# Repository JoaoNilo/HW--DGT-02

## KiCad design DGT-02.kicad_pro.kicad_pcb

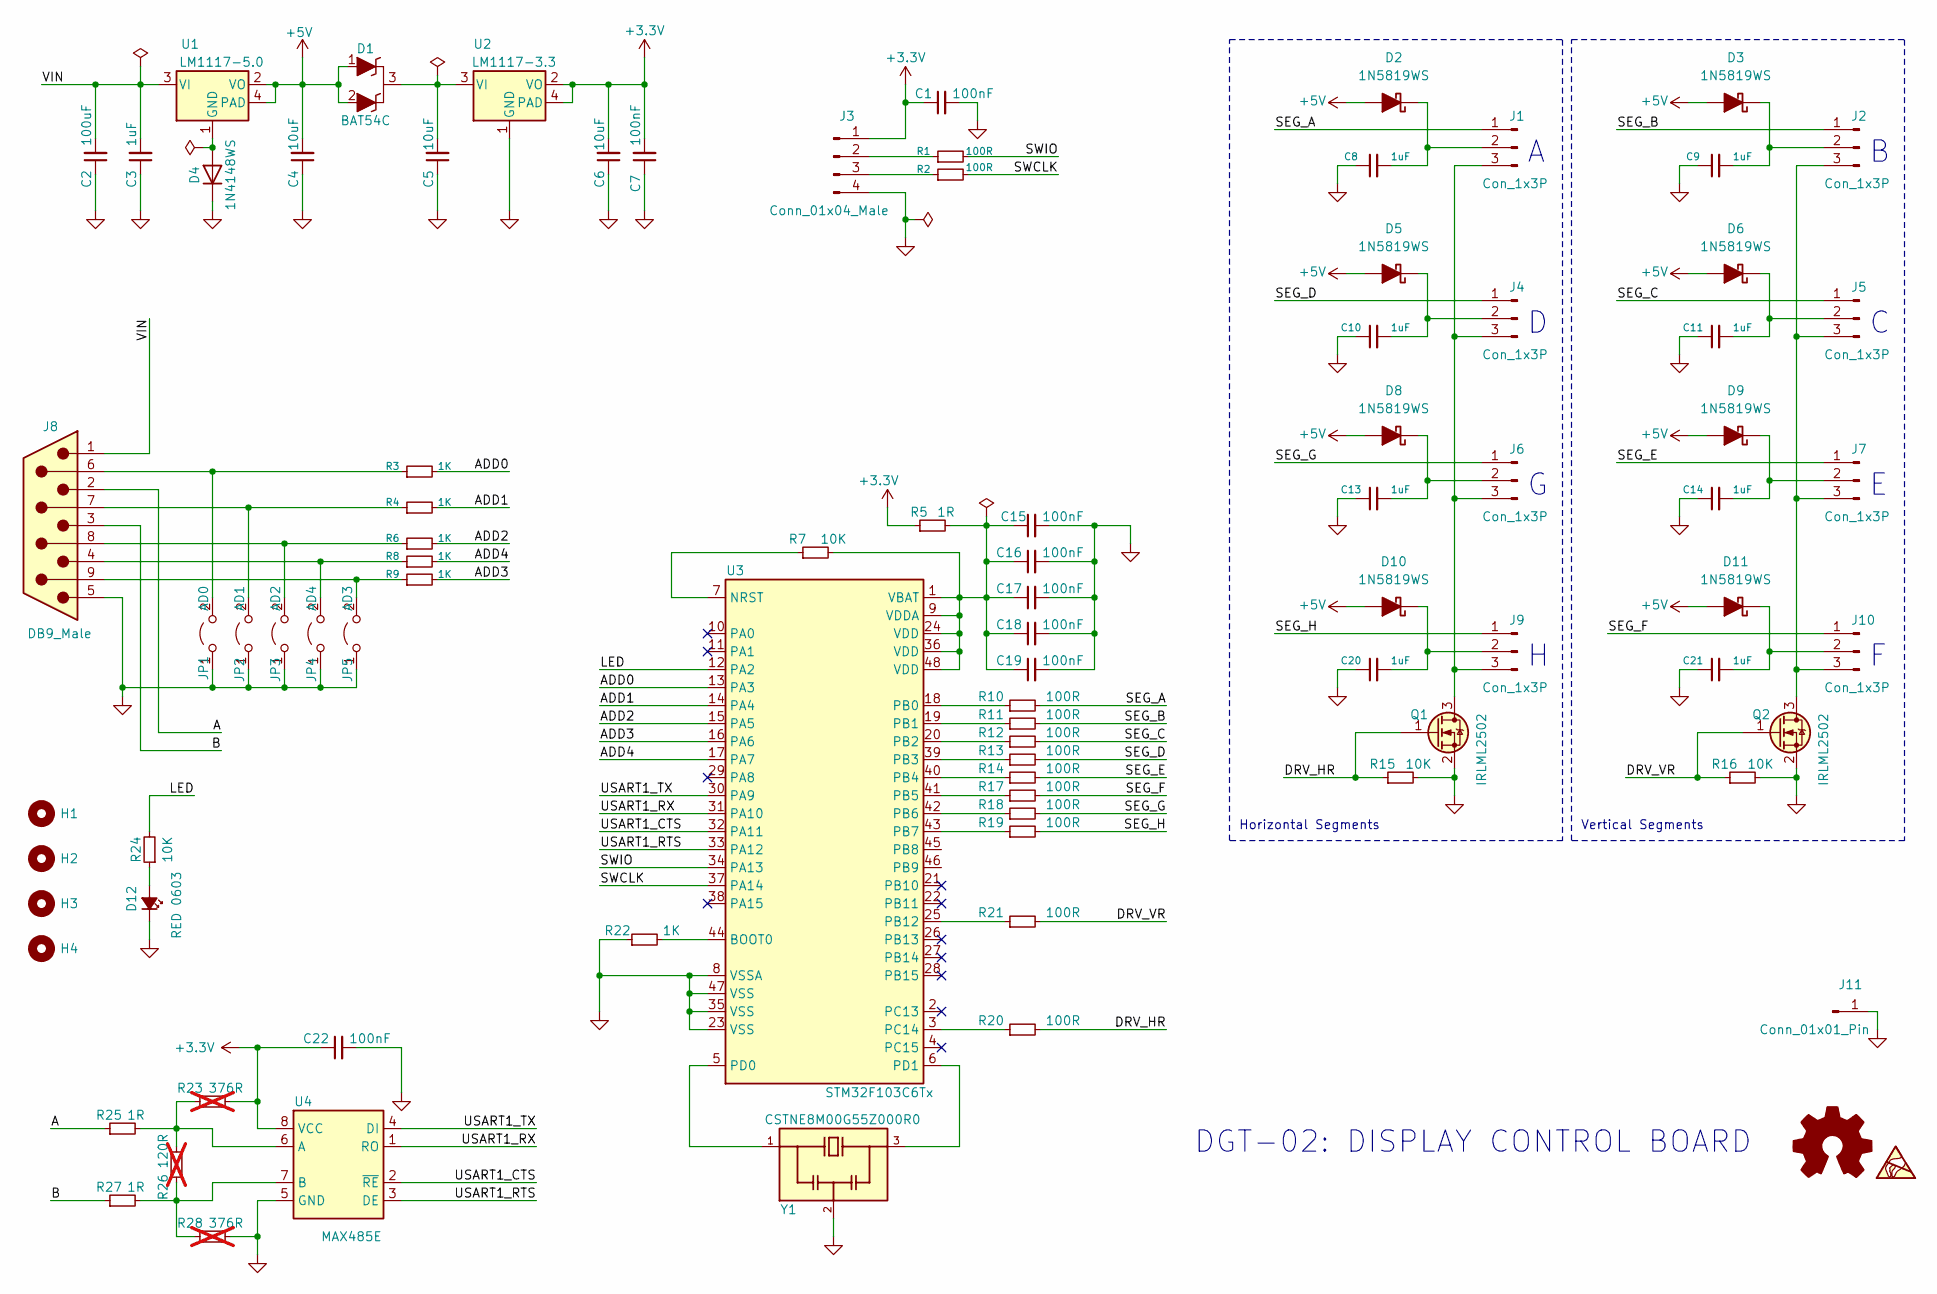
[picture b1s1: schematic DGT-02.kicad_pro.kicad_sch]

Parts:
C1, C7, C15, C16, C17, C18, C19, C22: 100nF; C_0603_1608Metric
C2: 100uF; C_1210_3225Metric
C3: 1uF; C_0805_2012Metric
C4, C5, C6: 10uF; C_1206_3216Metric
C8, C9, C10, C11, C13, C14, C20, C21: 1uF; C_0603_1608Metric
D1: BAT54C; SOT-23
D2, D3, D5, D6, D8, D9, D10, D11: 1N5819WS; D_SOD-323
D4: 1N4148WS; D_SOD-323
D12: RED 0603; LED_0603_1608Metric
H1, H2, H3, H4: MountingHole; MountingHole_2.2mm_M2
J1, J2, J4, J5, J6, J7, J9, J10: Con_1x3P; PinHeader_1x03_P2.54mm_Horizontal_Nilo
J3: Conn_01x04_Male; PinHeader_1x04_P2.54mm_Vertical
J8: DB9_Male; DSUB-9_Male_Horizontal_P2.77x2.84mm_EdgePinOffset7.70mm_Hou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
J11: Conn_01x01_Pin; PinHeader_1x01_P2.54mm_Vertical
JP1: AD0; SolderJumper-2_P1.3mm_Open_TrianglePad1.0x1.5mm
JP2: AD1; SolderJumper-2_P1.3mm_Open_TrianglePad1.0x1.5mm
JP3: AD2; SolderJumper-2_P1.3mm_Open_TrianglePad1.0x1.5mm
JP4: AD4; SolderJumper-2_P1.3mm_Open_TrianglePad1.0x1.5mm
JP5: AD3; SolderJumper-2_P1.3mm_Open_TrianglePad1.0x1.5mm
LOGO1: Logo_Open_Hardware_Small; KiCad-Logo2_5mm_SilkScreen
Q1, Q2: IRLML2502; SOT-23
R1, R2, R10, R11, R12, R13, R14, R17, R18, R19, R20, R21: 100R; R_0603_1608Metric
R3, R4, R6, R8, R9, R22: 1K; R_0603_1608Metric
R5, R25, R27: 1R; R_0603_1608Metric
R7, R15, R16, R24: 10K; R_0603_1608Metric
R23, R28: 376R; R_0603_1608Metric; not fitted
R26: 120R; R_0603_1608Metric; not fitted
SYM1: SYM_ESD_Small; ESD-Logo_6.6x6mm_SilkScreen
U1: LM1117-5.0; SOT-223
U2: LM1117-3.3; SOT-223
U3: STM32F103C6Tx; LQFP-48_7x7mm_P0.5mm
U4: MAX485E; SOIC-8_3.9x4.9mm_P1.27mm
Y1: CSTNE8M00G55Z000R0; OSC_CSTNE8M00G55Z000R0; PARTREV JGC42-8858A

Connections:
+3V3: C1.1, C6.2, C7.2, C22.1, J3.1, R5.1, R23.2, U2.2 (VO), U2.4 (PAD), U4.8 (VCC)
+5V: C4.2, D1.1 (A), D1.2 (A), D2.2 (A), D3.2 (A), D5.2 (A), D6.2 (A), D8.2 (A), D9.2 (A), D10.2 (A), D11.2 (A), U1.2 (VO), U1.4 (PAD)
/A: J8.2, R25.1
/ADD0: R3.2, U3.13 (PA3)
/ADD1: R4.2, U3.14 (PA4)
/ADD2: R6.2, U3.15 (PA5)
/ADD3: R9.2, U3.16 (PA6)
/ADD4: R8.2, U3.17 (PA7)
/B: J8.3, R27.1
/DRV_HR: Q1.1 (G), R15.1, R20.2
/DRV_VR: Q2.1 (G), R16.1, R21.2
/LED: R24.2, U3.12 (PA2)
/SEG_A: J1.1, R10.2
/SEG_B: J2.1, R11.2
/SEG_C: J5.1, R12.2
/SEG_D: J4.1, R13.2
/SEG_E: J7.1, R14.2
/SEG_F: J10.1, R17.2
/SEG_G: J6.1, R18.2
/SEG_H: J9.1, R19.2
/SWCLK: R2.2, U3.37 (PA14)
/SWIO: R1.2, U3.34 (PA13)
/USART1_CTS: U3.32 (PA11), U4.2 (~RE)
/USART1_RTS: U3.33 (PA12), U4.3 (DE)
/USART1_RX: U3.31 (PA10), U4.1 (RO)
/USART1_TX: U3.30 (PA9), U4.4 (DI)
/VIN: C2.2, C3.2, J8.1, U1.3 (VI)
unnamed: C5.2, D1.3 (K), U2.3 (VI)
unnamed: C8.2, D2.1 (K), J1.2
unnamed: C9.2, D3.1 (K), J2.2
unnamed: D4.2 (A), U1.1 (GND)
unnamed: C10.2, D5.1 (K), J4.2
unnamed: C11.2, D6.1 (K), J5.2
unnamed: C13.2, D8.1 (K), J6.2
unnamed: C14.2, D9.1 (K), J7.2
unnamed: C20.2, D10.1 (K), J9.2
unnamed: C21.2, D11.1 (K), J10.2
unnamed: D12.2 (A), R24.1
unnamed: J3.2, R1.1
unnamed: J3.3, R2.1
unnamed: J8.6, JP1.2 (B), R3.1
unnamed: J8.7, JP2.2 (B), R4.1
unnamed: J8.8, JP3.2 (B), R6.1
unnamed: J8.4, JP4.2 (B), R8.1
unnamed: J8.9, JP5.2 (B), R9.1
unnamed: R22.2, U3.44 (BOOT0)
unnamed: R7.1, U3.7 (NRST)
unnamed: R10.1, U3.18 (PB0)
unnamed: R11.1, U3.19 (PB1)
unnamed: R12.1, U3.20 (PB2)
unnamed: R13.1, U3.39 (PB3)
unnamed: R14.1, U3.40 (PB4)
unnamed: R17.1, U3.41 (PB5)
unnamed: R18.1, U3.42 (PB6)
unnamed: R19.1, U3.43 (PB7)
unnamed: R21.1, U3.25 (PB12)
unnamed: R20.1, U3.3 (PC14)
unnamed: U3.5 (PD0), Y1.1
unnamed: U3.6 (PD1), Y1.3
unnamed: C15.1, C16.1, C17.1, C18.1, C19.1, R5.2, R7.2, U3.1 (VBAT), U3.9 (VDDA), U3.24 (VDD), U3.36 (VDD), U3.48 (VDD)
unnamed: R23.1, R25.2, R26.2, U4.6 (A)
unnamed: R26.1, R27.2, R28.1, U4.7 (B)

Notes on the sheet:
Vertical Segments
Horizontal Segments
DGT-02: DISPLAY CONTROL BOARD

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
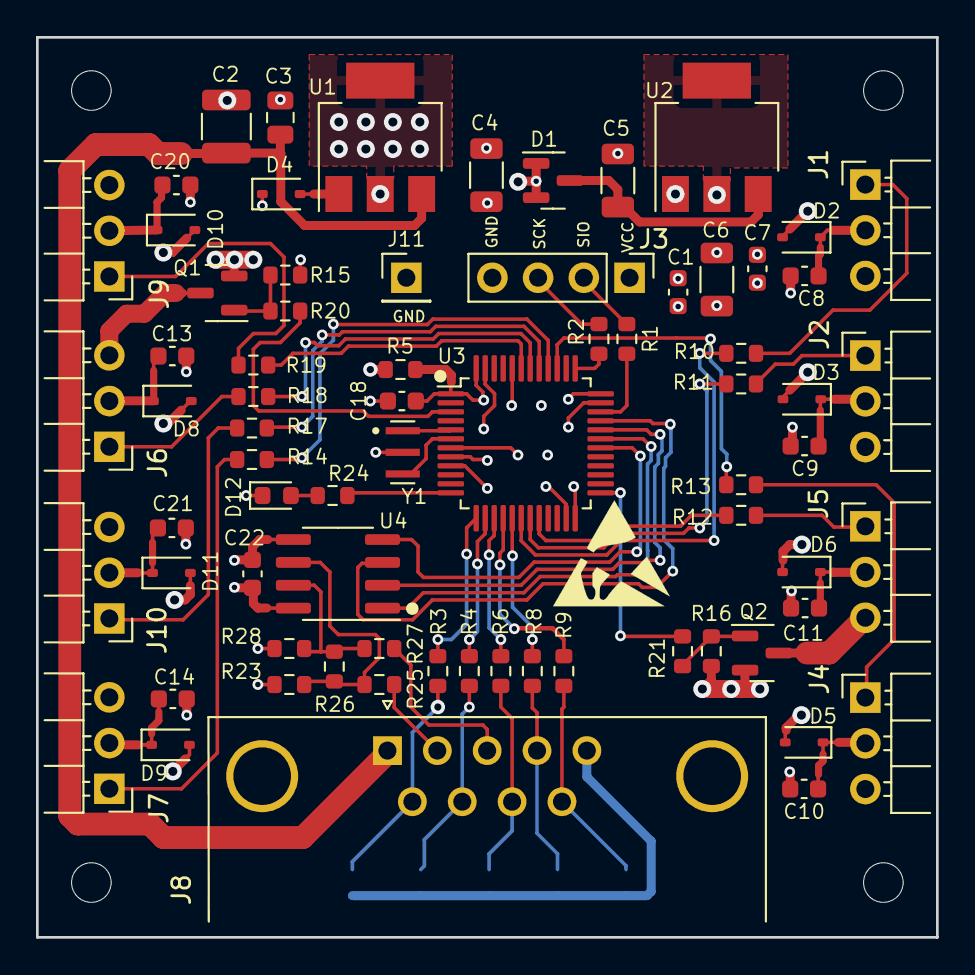
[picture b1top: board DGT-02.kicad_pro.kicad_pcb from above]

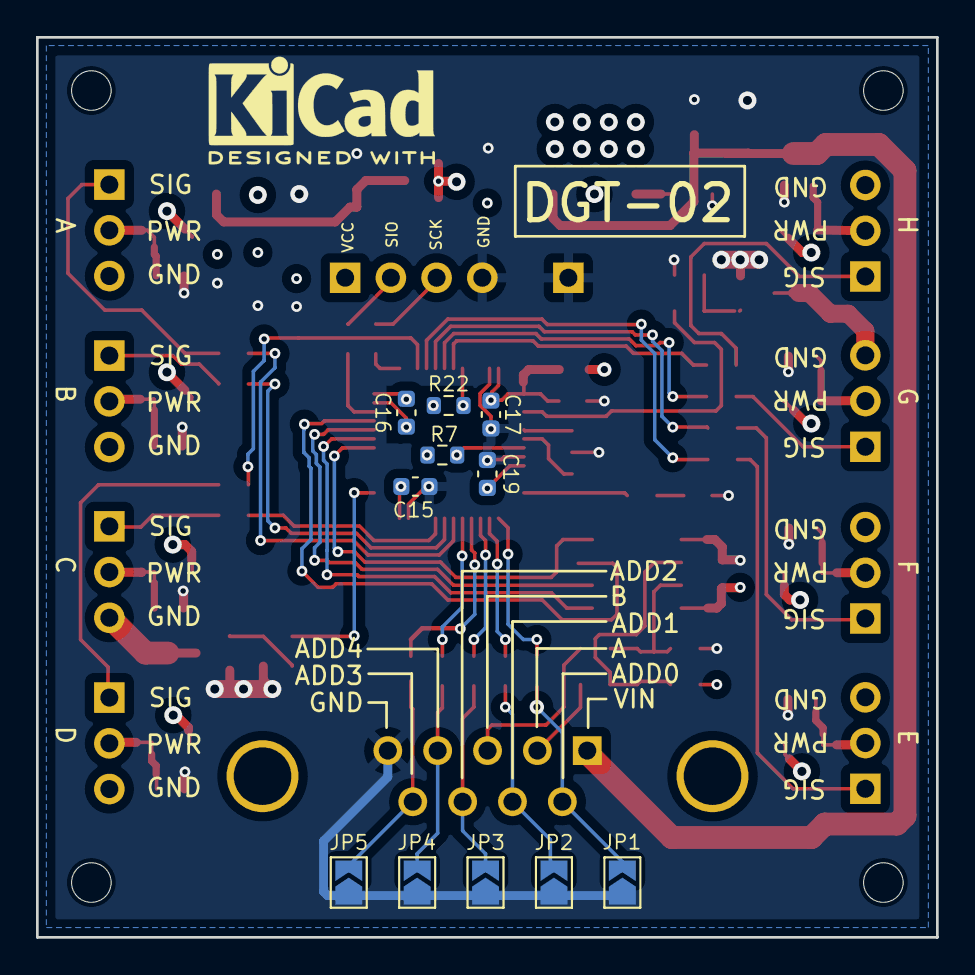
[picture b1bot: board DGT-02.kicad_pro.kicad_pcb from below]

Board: 4 copper layers, 50.0 x 50.0 mm, 89 parts (12 on the bottom side), 65 nets.

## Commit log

2023-12-02 initial commit.
2023-12-02 Alterada a cor do label do diodo D4
